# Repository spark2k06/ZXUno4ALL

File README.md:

# ZXUno4ALL

Spanish
-------

Todos los ficheros correspondientes a ZXUno4ALL compartidos en este repositorio tienen licencia GNU v3.0 salvo que se indique lo contrario.

La principal idea de ZXUno4ALL es facilitar y poner al alcance de cualquiera los desarrollos de cores y software creado para el ZXUno, mediante el uso de diferentes formatos de backplanes que hacen uso del modulo principal ZXUnCore. Dadas las carecterísticas de éste, es posible crear proyectos derivados que no guarden relación con el ZXUno.

Página principal de ZXUno:

http://zxuno.speccy.org/

Cores desarrollados para ZXUno:

https://github.com/zxdos/zxuno

English
-------

All the files corresponding to ZXUno4ALL shared in this repository are licensed under GNU v3.0 unless otherwise indicated.

The main idea of ZXUno4ALL is to facilitate and make available to anyone the development of cores and software created for the ZXUno, through the use of different backplane formats that make use of the main module ZXUnCore. Given its characteristics, it is possible to create derivative projects that are not related to the ZXUno.

ZXUno Home Page:

http://zxuno.speccy.org/

Cores developed for ZXUno:

https://github.com/zxdos/zxuno

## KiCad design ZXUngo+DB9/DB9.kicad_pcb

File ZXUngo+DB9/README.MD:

# ZXUnGo+ DB9

License is Creative Commons by SA.

Spanish
-------

Addon para ZXUnCore y ZXUnGo+ con conector de Joystick, compatible con splitter de Antonio Villena.

English
-------

Addon for ZXUnCore and ZXUnGo+ with Joystick connector, compatible with Antonio Villena splitter.

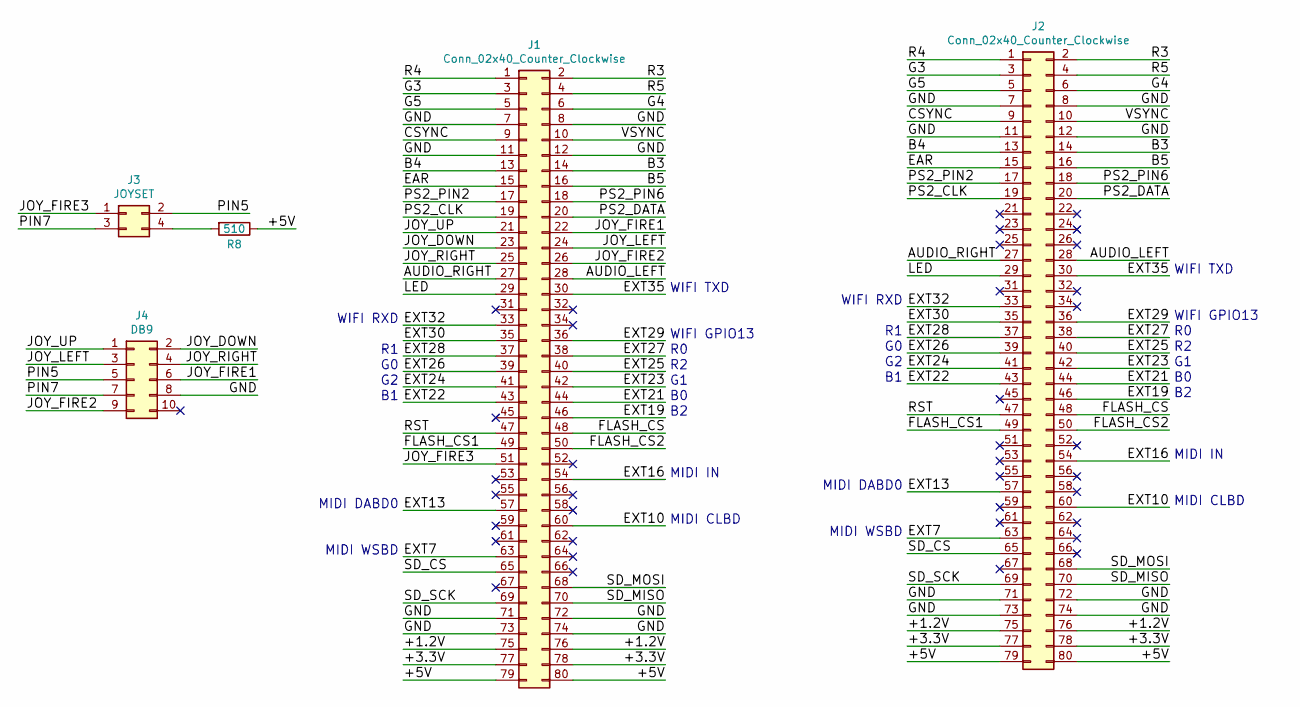
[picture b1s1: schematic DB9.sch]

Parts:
J1: Conn_02x40_Counter_Clockwise; PinHeader_2x40_P2.00mm_Horizontal
J2: Conn_02x40_Counter_Clockwise; PinSocket_2x40_P2.00mm_Horizontal_Custom
J3: JOYSET; PinHeader_2x02_P2.54mm_Vertical
J4: DB9; PinHeader_2x05_P2.54mm_Horizontal
R8: 510; R_0603_1608Metric

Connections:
/+1.2V: J1.75, J1.76, J2.75, J2.76
/+3.3V: J1.77, J1.78, J2.77, J2.78
/+5V: J1.79, J1.80, J2.79, J2.80, R8.1
/AUDIO_LEFT: J1.28, J2.28
/AUDIO_RIGHT: J1.27, J2.27
/B3: J1.14, J2.14
/B4: J1.13, J2.13
/B5: J1.16, J2.16
/CSYNC: J1.9, J2.9
/EAR: J1.15, J2.15
/EXT7: J1.63, J2.63
/EXT10: J1.60, J2.60
/EXT13: J1.57, J2.57
/EXT16: J1.54, J2.54
/EXT19: J1.46, J2.46
/EXT21: J1.44, J2.44
/EXT22: J1.43, J2.43
/EXT23: J1.42, J2.42
/EXT24: J1.41, J2.41
/EXT25: J1.40, J2.40
/EXT26: J1.39, J2.39
/EXT27: J1.38, J2.38
/EXT28: J1.37, J2.37
/EXT29: J1.36, J2.36
/EXT30: J1.35, J2.35
/EXT32: J1.33, J2.33
/EXT35: J1.30, J2.30
/FLASH_CS: J1.48, J2.48
/FLASH_CS1: J1.49, J2.49
/FLASH_CS2: J1.50, J2.50
/G3: J1.3, J2.3
/G4: J1.6, J2.6
/G5: J1.5, J2.5
/GND: J1.7, J1.8, J1.11, J1.12, J1.71, J1.72, J1.73, J1.74, J2.7, J2.8, J2.11, J2.12, J2.71, J2.72, J2.73, J2.74, J4.8
/JOY_DOWN: J1.23, J4.2
/JOY_FIRE1: J1.22, J4.6
/JOY_FIRE2: J1.26, J4.9
/JOY_FIRE3: J1.51, J3.1
/JOY_LEFT: J1.24, J4.3
/JOY_RIGHT: J1.25, J4.4
/JOY_UP: J1.21, J4.1
/LED: J1.29, J2.29
/PIN5: J3.2, J4.5
/PIN7: J3.3, J4.7
/PS2_CLK: J1.19, J2.19
/PS2_DATA: J1.20, J2.20
/PS2_PIN2: J1.17, J2.17
/PS2_PIN6: J1.18, J2.18
/R3: J1.2, J2.2
/R4: J1.1, J2.1
/R5: J1.4, J2.4
/RST: J1.47, J2.47
/SD_CS: J1.65, J2.65
/SD_MISO: J1.70, J2.70
/SD_MOSI: J1.68, J2.68
/SD_SCK: J1.69, J2.69
/VSYNC: J1.10, J2.10
unnamed: J3.4, R8.2

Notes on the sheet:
MIDI CLBD
MIDI IN
WIFI GPIO13
WIFI TXD
WIFI RXD
MIDI WSBD
MIDI DABD0

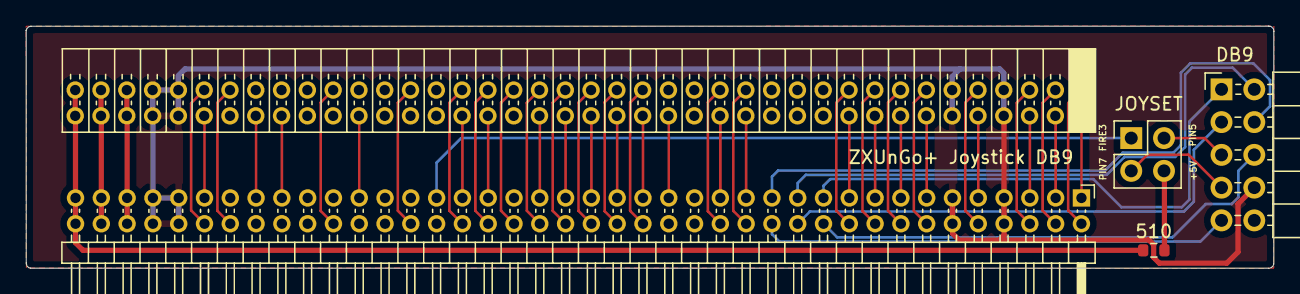
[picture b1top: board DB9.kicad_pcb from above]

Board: 2 copper layers, 96.8 x 18.8 mm, 5 parts (0 on the bottom side), 58 nets.

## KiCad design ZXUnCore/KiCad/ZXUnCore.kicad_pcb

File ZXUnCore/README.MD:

# ZXUno4ALL

License is Creative Commons by SA.

PINOUT (ZXUNO RGB666) / GRAPHICS GREMLIN
----------------------------------------

Spanish
-------

Se trata de un proyecto que hace uso de la FPGA Xilinx Spartan XC6SLX9-2TQG144C y ha sido desarrollado con la finalidad de ser 100% compatible con los cores desarrollados para el ZXUno. Los esquemáticos están basados en éste, gracias al trabajo previo que llevó a cabo K_Mirror con la migración del proyecto del ZXUno 4.1 a KiCad.

A diferencia del ZXUno original, ZXUnCore tiene un formato modular y está pensado para facilitar la integración en otros proyectos derivados del mismo, dentro del proyecto global denominado ZXUno4ALL. No obstante, al quedar expuestos casi todos los pines I/O de la FPGA, éste puede ser utilizado en otros proyectos basados en esta FPGA.

ZXUnCore dispone de un conector de 2x40 pines y paso de 2.0mm, lo cual hace posible que se pueda conectar encima o debajo del backplane del proyecto derivado de forma horizontal. También vertical u horizontal al mismo nivel de la base del proyecto derivado, empleando en este caso un conector de ángulo recto o acodado.

English
-------

This is a project that uses the Xilinx Spartan XC6SLX9-2TQG144C FPGA and has been developed with the aim of being 100% compatible with the cores developed for the ZXUno. The schematics are based on this, thanks to the previous work carried out by K_Mirror with the migration of the project from ZXUno 4.1 to KiCad.

Unlike the original ZXUno, ZXUnCore has a modular format and is designed to facilitate integration into other projects derived from it, within the global project called ZXUno4ALL. However, since almost all the I/O pins of the FPGA are exposed, it can be used in other projects based on this FPGA.

ZXUnCore has a 2x40-pin connector and 2.0mm pitch, which makes it possible to connect above or below the backplane of the derived project horizontally. Also vertically or horizontally at the same level as the base of the derived project, in this case using a right-angle or angled connector.

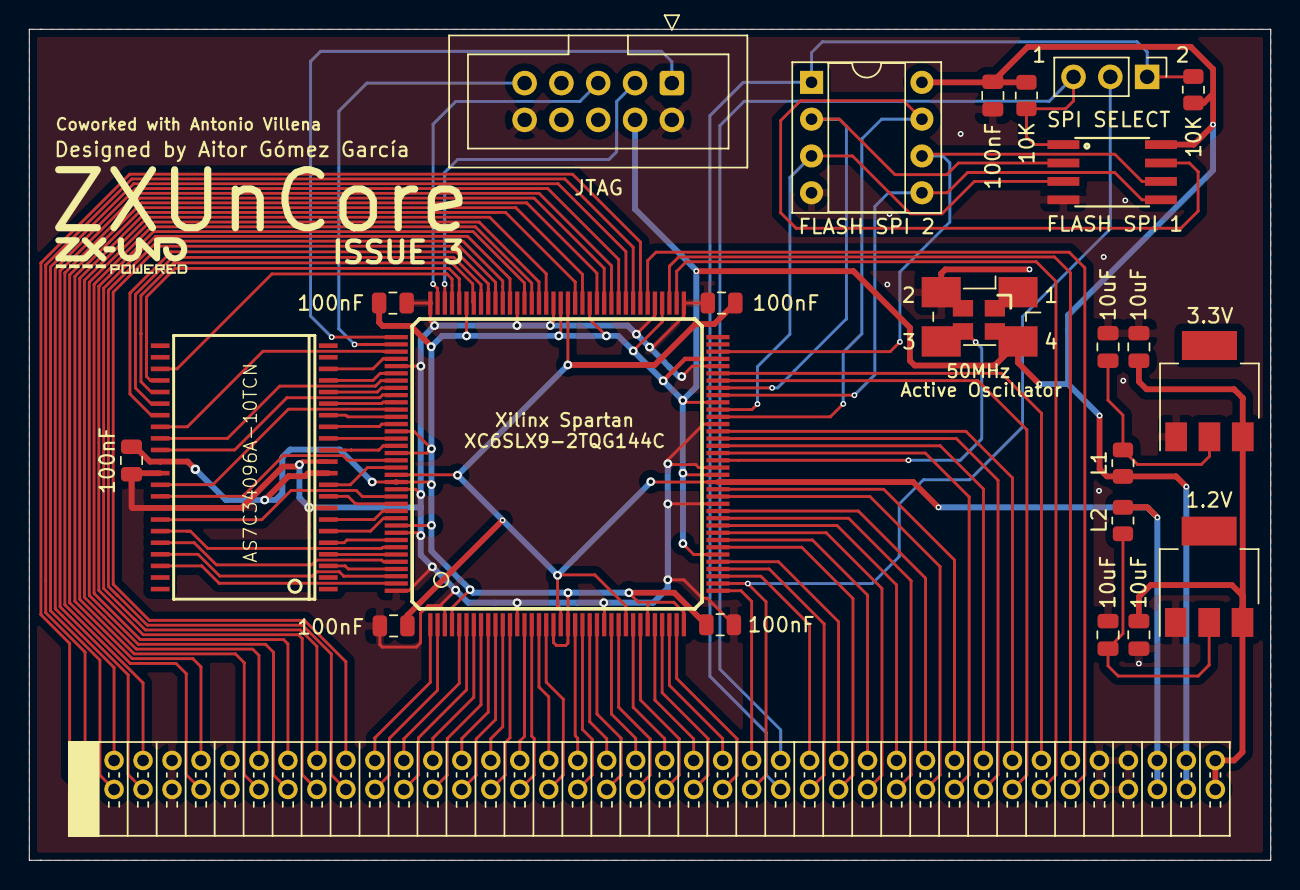
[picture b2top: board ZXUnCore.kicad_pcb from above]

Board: 2 copper layers, 85.7 x 57.3 mm, 26 parts (0 on the bottom side), 112 nets.

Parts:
C1, C3, C4, C5, C6, C7: 100nF; C_0805_2012Metric
C8, C9, C10, C11: 10uF; C_0805_2012Metric
G1: LOGO; PoweredByZXUno
J1: Conn_02x40_Counter_Clockwise; PinSocket_2x40_P2.00mm_Horizontal_Custom
J2: SPI SELECT; PinHeader_1x03_P2.54mm_Vertical
J3: JTAG; IDC-Header_2x05_P2.54mm_Vertical
L1, L2: 1K; R_0805_2012Metric
R1, R2: 10K; R_0805_2012Metric
U1: 6SLX9TQG144; TQ144
U2: FLASH SPI 2; DIP-8_W7.62mm_Socket
U3: AS7C34096A-10TCN; TSOP44-II
U4: FLASH SPI 1; SO08-EIAJ
U5: 50MHz; Crystal_SMD_0603-4Pin_6.0x3.5mm_HandSoldering
U6: 3.3V; SOT-223
U7: 1.2V; SOT-223
U8: 50MHz; TSX-3225

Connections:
+1V2: C5.1, C7.1, J1.75, J1.76, L2.1, U1.19, U1.28, U1.52, U1.89, U1.128
+3V3: C1.2, C3.1, C4.1, C6.1, J1.77, J1.78, J3.4, L1.1, R1.2, R2.2, U1.4, U1.18, U1.20, U1.31, U1.36, U1.42, U1.53, U1.63, U1.69, U1.76, U1.86, U1.90, U1.103, U1.122, U1.125, U1.129, U1.135, U2.8, U3.11, U3.33, U4.8, U5.4, U8.4
+5V: C8.1, C10.1, J1.79, J1.80, U6.3, U7.3
/AUDIO_LEFT: J1.28, U1.10
/AUDIO_RIGHT: J1.27, U1.9
/B3: J1.14, U1.88
/B4: J1.13, U1.92
/B5: J1.16, U1.93
/CLK: U1.55, U5.3, U8.3
/CSYNC: J1.9, U1.87
/EAR: J1.15, U1.94
/EXT6: J1.64, U1.58
/EXT7: J1.63, U1.57
/EXT8: J1.62, U1.56
/EXT9: J1.61, U1.51
/EXT10: J1.60, U1.50
/EXT11: J1.59, U1.48
/EXT12: J1.58, U1.47
/EXT13: J1.57, U1.46
/EXT14: J1.56, U1.45
/EXT15: J1.55, U1.44
/EXT16: J1.54, U1.43
/EXT17: J1.53, U1.41
/EXT18: J1.52, U1.40
/EXT19: J1.46, U1.35
/EXT20: J1.45, U1.34
/EXT21: J1.44, U1.33
/EXT22: J1.43, U1.32
/EXT23: J1.42, U1.30
/EXT24: J1.41, U1.29
/EXT25: J1.40, U1.27
/EXT26: J1.39, U1.26
/EXT27: J1.38, U1.24
/EXT28: J1.37, U1.23
/EXT29: J1.36, U1.22
/EXT30: J1.35, U1.21
/EXT31: J1.34, U1.17
/EXT32: J1.33, U1.16
/EXT33: J1.32, U1.15
/EXT34: J1.31, U1.14
/EXT35: J1.30, U1.12
/FLASH_CS: J1.48, J2.2, U1.38
/FLASH_CS1: J1.49, J2.3, R2.1, U4.1
/FLASH_CS2: J1.50, J2.1, R1.1, U2.1
/FLASH_HOLD: U1.61, U2.7, U4.7
/FLASH_MISO: U1.65, U2.2, U4.2
/FLASH_MOSI: U1.64, U2.5, U4.5
/FLASH_SCK: U1.70, U2.6, U4.6
/FLASH_WP: U1.62, U2.3, U4.3
/G3: J1.3, U1.82
/G4: J1.6, U1.83
/G5: J1.5, U1.84
/JOY_DOWN: J1.23, U1.5
/JOY_FIRE1: J1.22, U1.2
/JOY_FIRE2: J1.26, U1.8
/JOY_FIRE3: J1.51, U1.39
/JOY_LEFT: J1.24, U1.6
/JOY_RIGHT: J1.25, U1.7
/JOY_UP: J1.21, U1.1
/LED: J1.29, U1.11
/PS2_CLK: J1.19, U1.99
/PS2_DATA: J1.20, U1.98
/PS2_PIN2: J1.17, U1.97
/PS2_PIN6: J1.18, U1.95
/R3: J1.2, U1.79
/R4: J1.1, U1.80
/R5: J1.4, U1.81
/RST: J1.47, U1.37
/SD_CS: J1.65, U1.59
/SD_MISO: J1.70, U1.78
/SD_MOSI: J1.68, U1.74
/SD_SCK: J1.69, U1.75
/STDN: J1.66, U1.66
/STDNB: J1.67, U1.67
/TCK: J3.1, U1.109
/TDI: J3.9, U1.110
/TDO: J3.3, U1.106
/TMS: J3.5, U1.107
/VSYNC: J1.10, U1.85
/WR: U1.121, U3.15
/XA0: U1.141, U3.3
/XA1: U1.139, U3.4
/XA2: U1.137, U3.5
/XA3: U1.134, U3.6
/XA4: U1.133, U3.7
/XA5: U1.120, U3.16
/XA6: U1.118, U3.17
/XA7: U1.116, U3.18
/XA8: U1.114, U3.19
/XA9: U1.112, U3.20
/XA10: U1.104, U3.26
/XA11: U1.102, U3.27
/XA12: U1.101, U3.28
/XA13: U1.100, U3.29
/XA14: U1.111, U3.30
/XA15: U1.131, U3.38
/XA16: U1.138, U3.39
/XA17: U1.140, U3.40
/XA18: U1.142, U3.41
/XA19: U1.105, U3.25
/XA20: U1.143, U3.42
/XD0: U1.132, U3.9
/XD1: U1.127, U3.10
/XD2: U1.124, U3.13
/XD3: U1.123, U3.14
/XD4: U1.115, U3.31
/XD5: U1.117, U3.32
/XD6: U1.119, U3.35
/XD7: U1.126, U3.36
GND: C1.1, C3.2, C4.2, C5.2, C6.2, C7.2, C8.2, C9.2, C10.2, C11.2, J1.7, J1.8, J1.11, J1.12, J1.71, J1.72, J1.73, J1.74, J3.2, J3.10, U1.3, U1.13, U1.25, U1.49, U1.54, U1.60, U1.68, U1.73, U1.77, U1.91, U1.96, U1.108, U1.113, U1.130, U1.136, U1.144, U2.4, U3.8, U3.12, U3.34, U3.37, U4.4, U5.2, U6.1, U7.1, U8.2
unnamed: C9.1, L1.2, U6.2
unnamed: C11.1, L2.2, U7.2

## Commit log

2021-06-21 Cores específicos para ZXUnCore y compatibles
2021-09-26 ZXUno4All Manuals v1.0
2021-09-30 Manual v1.0.1 Added ePub Fix for wrong anchors Small corrections
2021-10-03 Manual v1.1.0 Added new ZX81 and ZX80 core Added joystick keys table Small Corrections
2021-11-23 Manual v1.1.1 Fixes and corrections Reordered cores Expanded link list
2021-12-29 Compatibilidad SD estandar
    * Compatibilidad con tarjetas de memoria SD estandar, menores de 4GB.
2022-02-18 Manual v1.2.0 Added PC XT CGA Core Spelling corrections
2022-02-19 Actualizacion de binarios
2022-03-12 Manual v1.2.1 Added Ondra SPO 186 core
2022-03-19 Joystick DB9 para ZXUnGo+
2022-03-26 Manual v1.3.0 Added ZXUnGo+ DB9 Added Flappy Bird Core
2022-04-30 Manual v1.3.1 Added SD card format compatibility table
2023-10-20 Manual v1.4.0 Multiple enhancements and corrections
2024-09-23 Upgrading binaries to the latest releases

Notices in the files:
ZXUnCore/KiCad/ZXUnCore.kicad_pcb:
This product is under CC-BY-SA Licence.
